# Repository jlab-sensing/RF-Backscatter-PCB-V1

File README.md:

# WaDAR Tag V1

This repo consists of the backscatter tag PCBs used with the WaDAR sensing system. This repo is a submodule of [WaDAR](https://github.com/jlab-sensing/wadar). This is our first version of the tag used in WaDAR's sensing system.

## Versions Overview

Each version is archived upon PCB fabrication and assembly, ensuring traceability and reproducibility of hardware iterations.

### WaDAR_Tag_V1_0
- **Status**: Archived (Non-functional)
- **Description**: Initial prototype of backscatter tag PCB. Board is included for historical refernce; does not support functional operation.
- **Authors**: Josie Dominguez, jocadomi@ucsc.edu

### WaDAR_Tag_V1_1
- **Description**: First operational version of the backscatter tag. Oscillates at a fixed frequency of 2^n Hz, where n is determined by the selected oscillator. 
- **Authors**: Eric Vetha, evetha@ucsc.edu | Jack Lin, jlin143@ucsc.edu

### WaDAR_Tag_V1_2 
- **Description**: Enhanced version featuring an oscillator supporting a more flexible frequency range.
- **Authors**: Eric Vetha, evetha@ucsc.edu

---

>This README will be updated as more information becomes available.

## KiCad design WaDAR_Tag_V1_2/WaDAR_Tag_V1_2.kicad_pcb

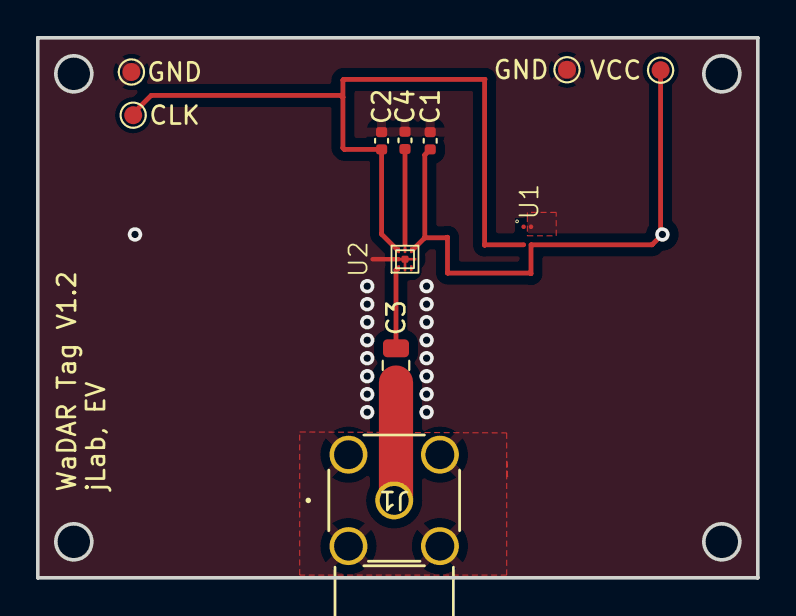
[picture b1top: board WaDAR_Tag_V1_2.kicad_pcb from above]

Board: 2 copper layers, 40.0 x 30.0 mm, 12 parts (1 on the bottom side), 6 nets.

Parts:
BT1: 1060; BatteryHolder_Keystone_1060_1x2032
C1, C2: CAP CER 33PF 0402; C_0402_1005Metric
C3: CAP CER 100PF 0805; C_0805_2012Metric
C4: CAP CER 100PF 0402; C_0402_1005Metric
CLK: CLK; TestPoint_Pad_D1.0mm
GND: GND; TestPoint_Pad_D1.0mm
GND#2: GND; TestPoint_Pad_D1.0mm
J1: 142-0701-321; CONN_SMA-J-P-H-RA-TH1_SAI
U1: SIT1569AC-J3-30E-0000.080000; SiT1569
U2: SKY13351-378LF; SKY13351_FP
VCC: VCC; TestPoint_Pad_D1.0mm

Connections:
GND: BT1.2 (-), C1.2, C2.2, C4.2, GND.1, GND#2.1, J1.2, J1.3, J1.4, J1.5, U1.4 (GND), U2.2 (GND)
unnamed: BT1.1 (+), C1.1, U1.3 (Vdd), U2.4 (VCTL2), VCC.1
unnamed: C3.2, J1.1
unnamed: C2.1, CLK.1, U1.2 (CLK_Out), U2.6 (VCTL1)
unnamed: C4.1, U2.5 (INPUT)
unnamed: C3.1, U2.1 (OUTPUT1)

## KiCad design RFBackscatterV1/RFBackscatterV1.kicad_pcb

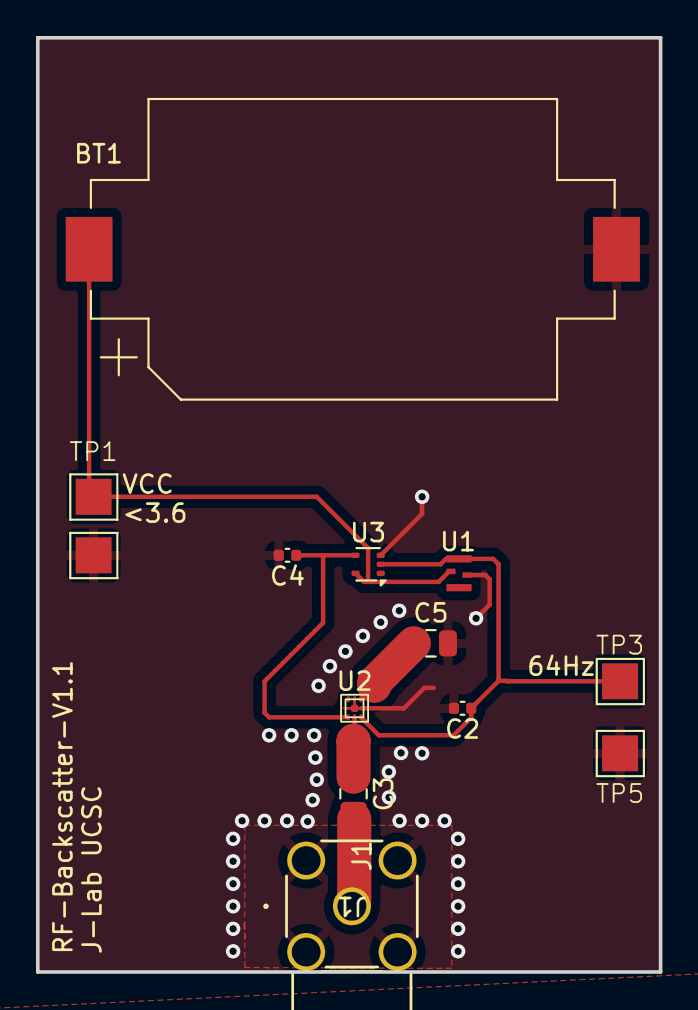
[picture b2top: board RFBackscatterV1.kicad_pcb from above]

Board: 2 copper layers, 34.6 x 51.9 mm, 13 parts (0 on the bottom side), 7 nets.

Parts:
BT1: Battery_Cell; BatteryHolder_Keystone_1060_1x2032
C2, C4: 33pF; C_0402_1005Metric
C3, C5: 10nF; C_0805_2012Metric
J1: SMA-J-P-H-RA-TH1; CONN_SMA-J-P-H-RA-TH1_SAI
TP1: VCC; EpicTestPointV1
TP3: CLK_OUT; EpicTestPointV1
TP5, TP6: GND; EpicTestPointV1
U1: SIT1534AI-H4-DCC-00.001E; XTAL4_SiT1533_SIT
U2: SKY13351_FP
U3: 74LVC1GU04DRL; SOT-553

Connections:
3V0: BT1.1 (+), TP1.1, U1.4 (Vdd), U3.5 (VCC)
GND: BT1.2 (-), C2.2, C4.2, C5.2, J1.2, J1.3, J1.4, J1.5, TP5.1, TP6.1, U1.2 (GND), U2.2 (GND), U3.3 (GND)
unnamed: C3.2, J1.1
unnamed: C2.1, TP3.1, U1.3 (CLK_Out), U2.6 (VCTL1), U3.2
unnamed: C3.1, U2.5 (INPUT)
unnamed: C5.1, U2.1 (OUTPUT1)
unnamed: C4.1, U2.4 (VCTL2), U3.4

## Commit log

2023-11-05 adding KiCAD project folder
2024-02-18 staging KiCAD files and new component library
2024-02-26 Added SiT1534
2024-02-26 Added BGSX33M5U16E6327XTSA1 and replaced low power oscillator
2024-07-05 Added SKY13351, finished initial schematic
2024-07-08 Finished SKY13351 footprint, staged board
2024-07-12 updated board, added buffer and filter capacitors
2024-07-12 generated manufacturing files for V1.0
2024-12-05 fixed input pin capacitor and RF connector ground
2024-12-05 fixed design
2024-12-05 1.1 added coin cell
2024-12-07 alexandre's changes; schematic awaiting confirmation
2024-12-07 DNP R1
2024-12-08 PCB updated
2024-12-08 alexandre's advice pt2
2024-12-08 pre-board review
2024-12-08 rename
2024-12-30 pre board review 2
2025-01-09 JLPCB order
2025-01-29 reorganizing
2025-01-29 renamed project files
2025-01-29 credited Jack
2025-01-29 updated schematic with SiT1569
2025-01-29 added footprint for SiT1549
2025-02-02 added test points, made PCB double sided
2025-02-05 updated datasheets
2025-02-05 fixed symbol lib errors
2025-02-05 fixed all absolute pathing issues
2025-02-05 updated version names
2025-02-05 added new RF junction
2025-02-05 updated capacitors and added mounting holes
2025-02-07 V_2 off to assembly
2025-02-23 fab files for V1_2
2025-02-23 updated README after V1_2
